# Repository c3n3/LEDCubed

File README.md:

# LEDCubed
LED^3

Hello person who wishes to learn the cube's ways! This will be a BRIEF introduction... Basically the situation is as follows: we have a cube, it is a 12 x 12 x 12 cube of RGB LEDs, we have this newly (but probably old when your reading this) created softare architecture that will hopefully stand the test of time (you decide). The things you want to look into are:
  
  App.h -> this contains the workings for how you make an 'App' for the cube, these can be animations, games, anything...
  The contained class is to be used as an abstract class and not to be used directly.
  
  Basic_Functions.h -> these are the low level functions that allow you to turn LEDs on and change their colors and such

If you fully understand what is in those two files you can start making apps. If you have trouble understanding what is going on just contact me, Caden Churchman, if you can possibly get my information (I'm definitly not writting it here).  

*************************
If you want to bypass the whole structure of the code, feel free to comment out the main loop of arduino and just test stuff there. (Thats probably the best way to learn what the heck is going on)
*************************

TODO:
  - Nest (Wrires)

  - More cool animations

  - 3d tetris

  - 3d minesweeper <----------------------------------- NEXT

  - oscilating 3d graph

  - Glass box

  - Maze/DoomMaze

Done:
  - Add links or files for the KiCad files that made the circuitry

  - Optimize code - Done?

  - Rolling Text Display - Done: TypeEngine

  - Stand - Done
  
  - Power inside stand - Done

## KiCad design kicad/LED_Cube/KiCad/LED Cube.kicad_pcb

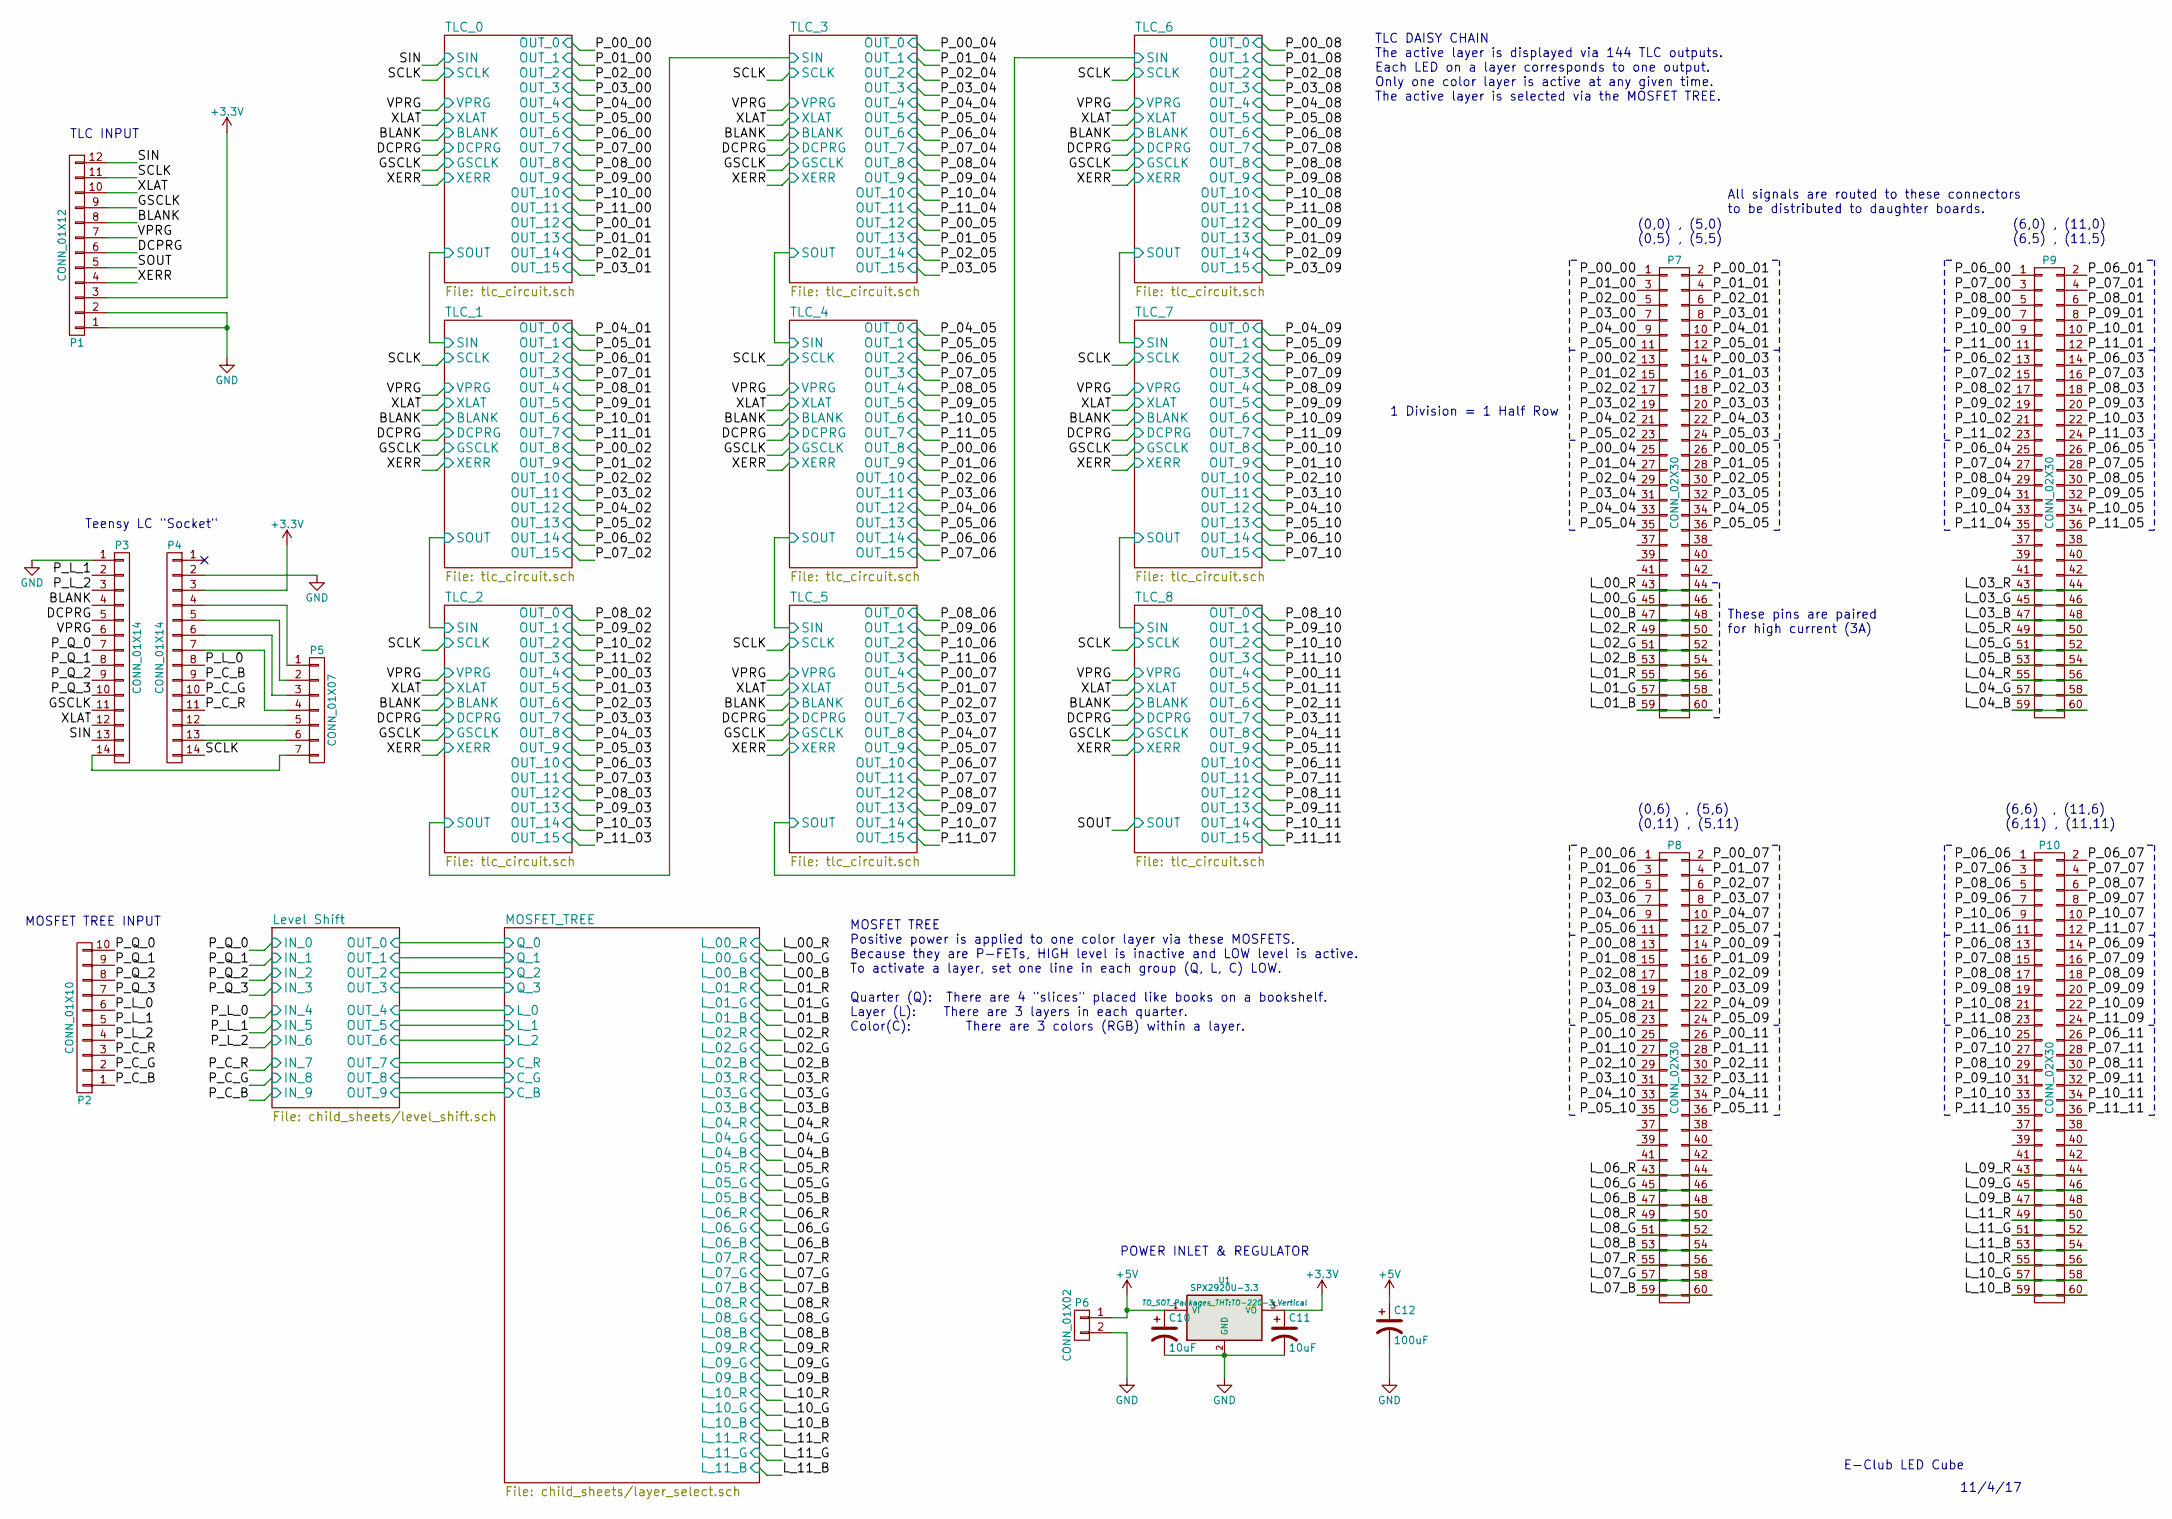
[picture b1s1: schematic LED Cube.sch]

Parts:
C10, C11: 10uF; CP_Radial_D5.0mm_P2.50mm
C12: 100uF; CP_Radial_D8.0mm_P3.50mm
P1: CONN_01X12; Pin_Header_Straight_1x12_Pitch2.54mm
P2: CONN_01X10; Pin_Header_Straight_1x10_Pitch2.54mm
P3, P4: CONN_01X14; Pin_Header_Straight_1x14_Pitch2.54mm
P5: CONN_01X07; Pin_Header_Straight_1x07_Pitch2.54mm
P6: CONN_01X02; TerminalBlock_bornier-2_P5.08mm
P7, P8, P9, P10: CONN_02X30; Pin_Header_Straight_2x30_Pitch2.54mm
U1: SPX2920U-3.3; TO-220-3_Vertical

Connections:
+3V3: C11.1, P1.3, P4.3, U1.3 (VO); also elsewhere on the board
+5V: C10.1, C12.1, P6.1, U1.1 (VI); also elsewhere on the board
/Level Shift/IN_0: P2.10, P3.7; also elsewhere on the board
/Level Shift/IN_1: P2.9, P3.8; also elsewhere on the board
/Level Shift/IN_2: P2.8, P3.9; also elsewhere on the board
/Level Shift/IN_3: P2.7, P3.10; also elsewhere on the board
/Level Shift/IN_4: P2.6, P4.8; also elsewhere on the board
/Level Shift/IN_5: P2.5, P3.2; also elsewhere on the board
/Level Shift/IN_6: P2.4, P3.3; also elsewhere on the board
/Level Shift/IN_7: P2.3, P4.11; also elsewhere on the board
/Level Shift/IN_8: P2.2, P4.10; also elsewhere on the board
/Level Shift/IN_9: P2.1, P4.9; also elsewhere on the board
/MOSFET_TREE/L_00_B: P7.47, P7.48; also elsewhere on the board
/MOSFET_TREE/L_00_G: P7.45, P7.46; also elsewhere on the board
/MOSFET_TREE/L_00_R: P7.43, P7.44; also elsewhere on the board
/MOSFET_TREE/L_01_B: P7.59, P7.60; also elsewhere on the board
/MOSFET_TREE/L_01_G: P7.57, P7.58; also elsewhere on the board
/MOSFET_TREE/L_01_R: P7.55, P7.56; also elsewhere on the board
/MOSFET_TREE/L_02_B: P7.53, P7.54; also elsewhere on the board
/MOSFET_TREE/L_02_G: P7.51, P7.52; also elsewhere on the board
/MOSFET_TREE/L_02_R: P7.49, P7.50; also elsewhere on the board
/MOSFET_TREE/L_03_B: P9.47, P9.48; also elsewhere on the board
/MOSFET_TREE/L_03_G: P9.45, P9.46; also elsewhere on the board
/MOSFET_TREE/L_03_R: P9.43, P9.44; also elsewhere on the board
/MOSFET_TREE/L_04_B: P9.59, P9.60; also elsewhere on the board
/MOSFET_TREE/L_04_G: P9.57, P9.58; also elsewhere on the board
/MOSFET_TREE/L_04_R: P9.55, P9.56; also elsewhere on the board
/MOSFET_TREE/L_05_B: P9.53, P9.54; also elsewhere on the board
/MOSFET_TREE/L_05_G: P9.51, P9.52; also elsewhere on the board
/MOSFET_TREE/L_05_R: P9.49, P9.50; also elsewhere on the board
/MOSFET_TREE/L_06_B: P8.47, P8.48; also elsewhere on the board
/MOSFET_TREE/L_06_G: P8.45, P8.46; also elsewhere on the board
/MOSFET_TREE/L_06_R: P8.43, P8.44; also elsewhere on the board
/MOSFET_TREE/L_07_B: P8.59, P8.60; also elsewhere on the board
/MOSFET_TREE/L_07_G: P8.57, P8.58; also elsewhere on the board
/MOSFET_TREE/L_07_R: P8.55, P8.56; also elsewhere on the board
/MOSFET_TREE/L_08_B: P8.53, P8.54; also elsewhere on the board
/MOSFET_TREE/L_08_G: P8.51, P8.52; also elsewhere on the board
/MOSFET_TREE/L_08_R: P8.49, P8.50; also elsewhere on the board
/MOSFET_TREE/L_09_B: P10.47, P10.48; also elsewhere on the board
/MOSFET_TREE/L_09_G: P10.45, P10.46; also elsewhere on the board
/MOSFET_TREE/L_09_R: P10.43, P10.44; also elsewhere on the board
/MOSFET_TREE/L_10_B: P10.59, P10.60; also elsewhere on the board
/MOSFET_TREE/L_10_G: P10.57, P10.58; also elsewhere on the board
/MOSFET_TREE/L_10_R: P10.55, P10.56; also elsewhere on the board
/MOSFET_TREE/L_11_B: P10.53, P10.54; also elsewhere on the board
/MOSFET_TREE/L_11_G: P10.51, P10.52; also elsewhere on the board
/MOSFET_TREE/L_11_R: P10.49, P10.50; also elsewhere on the board
/TLC_0/BLANK: P1.8, P3.4; also elsewhere on the board
/TLC_0/DCPRG: P1.6, P3.5; also elsewhere on the board
/TLC_0/GSCLK: P1.9, P3.11; also elsewhere on the board
/TLC_0/OUT_0: P7.1; also elsewhere on the board
/TLC_0/OUT_1: P7.3; also elsewhere on the board
/TLC_0/OUT_2: P7.5; also elsewhere on the board
/TLC_0/OUT_3: P7.7; also elsewhere on the board
/TLC_0/OUT_4: P7.9; also elsewhere on the board
/TLC_0/OUT_5: P7.11; also elsewhere on the board
/TLC_0/OUT_6: P9.1; also elsewhere on the board
/TLC_0/OUT_7: P9.3; also elsewhere on the board
/TLC_0/OUT_8: P9.5; also elsewhere on the board
/TLC_0/OUT_9: P9.7; also elsewhere on the board
/TLC_0/OUT_10: P9.9; also elsewhere on the board
/TLC_0/OUT_11: P9.11; also elsewhere on the board
/TLC_0/OUT_12: P7.2; also elsewhere on the board
/TLC_0/OUT_13: P7.4; also elsewhere on the board
/TLC_0/OUT_14: P7.6; also elsewhere on the board
/TLC_0/OUT_15: P7.8; also elsewhere on the board
/TLC_0/SCLK: P1.11, P4.14; also elsewhere on the board
/TLC_0/SIN: P1.12, P3.13; also elsewhere on the board
/TLC_0/VPRG: P1.7, P3.6; also elsewhere on the board
/TLC_0/XERR: P1.4; also elsewhere on the board
/TLC_0/XLAT: P1.10, P3.12; also elsewhere on the board
/TLC_1/OUT_0: P7.10; also elsewhere on the board
/TLC_1/OUT_1: P7.12; also elsewhere on the board
/TLC_1/OUT_2: P9.2; also elsewhere on the board
/TLC_1/OUT_3: P9.4; also elsewhere on the board
/TLC_1/OUT_4: P9.6; also elsewhere on the board
/TLC_1/OUT_5: P9.8; also elsewhere on the board
/TLC_1/OUT_6: P9.10; also elsewhere on the board
/TLC_1/OUT_7: P9.12; also elsewhere on the board
/TLC_1/OUT_8: P7.13; also elsewhere on the board
/TLC_1/OUT_9: P7.15; also elsewhere on the board
/TLC_1/OUT_10: P7.17; also elsewhere on the board
/TLC_1/OUT_11: P7.19; also elsewhere on the board
/TLC_1/OUT_12: P7.21; also elsewhere on the board
/TLC_1/OUT_13: P7.23; also elsewhere on the board
/TLC_1/OUT_14: P9.13; also elsewhere on the board
/TLC_1/OUT_15: P9.15; also elsewhere on the board
/TLC_2/OUT_0: P9.17; also elsewhere on the board
/TLC_2/OUT_1: P9.19; also elsewhere on the board
/TLC_2/OUT_2: P9.21; also elsewhere on the board
/TLC_2/OUT_3: P9.23; also elsewhere on the board
/TLC_2/OUT_4: P7.14; also elsewhere on the board
/TLC_2/OUT_5: P7.16; also elsewhere on the board
/TLC_2/OUT_6: P7.18; also elsewhere on the board
/TLC_2/OUT_7: P7.20; also elsewhere on the board
/TLC_2/OUT_8: P7.22; also elsewhere on the board
/TLC_2/OUT_9: P7.24; also elsewhere on the board
/TLC_2/OUT_10: P9.14; also elsewhere on the board
/TLC_2/OUT_11: P9.16; also elsewhere on the board
/TLC_2/OUT_12: P9.18; also elsewhere on the board
/TLC_2/OUT_13: P9.20; also elsewhere on the board
/TLC_2/OUT_14: P9.22; also elsewhere on the board
/TLC_2/OUT_15: P9.24; also elsewhere on the board
/TLC_3/OUT_0: P7.25; also elsewhere on the board
/TLC_3/OUT_1: P7.27; also elsewhere on the board
/TLC_3/OUT_2: P7.29; also elsewhere on the board
/TLC_3/OUT_3: P7.31; also elsewhere on the board
/TLC_3/OUT_4: P7.33; also elsewhere on the board
/TLC_3/OUT_5: P7.35; also elsewhere on the board
/TLC_3/OUT_6: P9.25; also elsewhere on the board
/TLC_3/OUT_7: P9.27; also elsewhere on the board
/TLC_3/OUT_8: P9.29; also elsewhere on the board
/TLC_3/OUT_9: P9.31; also elsewhere on the board
/TLC_3/OUT_10: P9.33; also elsewhere on the board
/TLC_3/OUT_11: P9.35; also elsewhere on the board
/TLC_3/OUT_12: P7.26; also elsewhere on the board
/TLC_3/OUT_13: P7.28; also elsewhere on the board
/TLC_3/OUT_14: P7.30; also elsewhere on the board
/TLC_3/OUT_15: P7.32; also elsewhere on the board
/TLC_4/OUT_0: P7.34; also elsewhere on the board
/TLC_4/OUT_1: P7.36; also elsewhere on the board
/TLC_4/OUT_2: P9.26; also elsewhere on the board
/TLC_4/OUT_3: P9.28; also elsewhere on the board
/TLC_4/OUT_4: P9.30; also elsewhere on the board
/TLC_4/OUT_5: P9.32; also elsewhere on the board
/TLC_4/OUT_6: P9.34; also elsewhere on the board
/TLC_4/OUT_7: P9.36; also elsewhere on the board
/TLC_4/OUT_8: P8.1; also elsewhere on the board
/TLC_4/OUT_9: P8.3; also elsewhere on the board
/TLC_4/OUT_10: P8.5; also elsewhere on the board
/TLC_4/OUT_11: P8.7; also elsewhere on the board
/TLC_4/OUT_12: P8.9; also elsewhere on the board
/TLC_4/OUT_13: P8.11; also elsewhere on the board
/TLC_4/OUT_14: P10.1; also elsewhere on the board
/TLC_4/OUT_15: P10.3; also elsewhere on the board
/TLC_5/OUT_0: P10.5; also elsewhere on the board
/TLC_5/OUT_1: P10.7; also elsewhere on the board
/TLC_5/OUT_2: P10.9; also elsewhere on the board
/TLC_5/OUT_3: P10.11; also elsewhere on the board
/TLC_5/OUT_4: P8.2; also elsewhere on the board
/TLC_5/OUT_5: P8.4; also elsewhere on the board
/TLC_5/OUT_6: P8.6; also elsewhere on the board
/TLC_5/OUT_7: P8.8; also elsewhere on the board
/TLC_5/OUT_8: P8.10; also elsewhere on the board
/TLC_5/OUT_9: P8.12; also elsewhere on the board
/TLC_5/OUT_10: P10.2; also elsewhere on the board
/TLC_5/OUT_11: P10.4; also elsewhere on the board
/TLC_5/OUT_12: P10.6; also elsewhere on the board
/TLC_5/OUT_13: P10.8; also elsewhere on the board
/TLC_5/OUT_14: P10.10; also elsewhere on the board
/TLC_5/OUT_15: P10.12; also elsewhere on the board
/TLC_6/OUT_0: P8.13; also elsewhere on the board
/TLC_6/OUT_1: P8.15; also elsewhere on the board
/TLC_6/OUT_2: P8.17; also elsewhere on the board
/TLC_6/OUT_3: P8.19; also elsewhere on the board
/TLC_6/OUT_4: P8.21; also elsewhere on the board
/TLC_6/OUT_5: P8.23; also elsewhere on the board
/TLC_6/OUT_6: P10.13; also elsewhere on the board
/TLC_6/OUT_7: P10.15; also elsewhere on the board
/TLC_6/OUT_8: P10.17; also elsewhere on the board
/TLC_6/OUT_9: P10.19; also elsewhere on the board
/TLC_6/OUT_10: P10.21; also elsewhere on the board
/TLC_6/OUT_11: P10.23; also elsewhere on the board
/TLC_6/OUT_12: P8.14; also elsewhere on the board
/TLC_6/OUT_13: P8.16; also elsewhere on the board
/TLC_6/OUT_14: P8.18; also elsewhere on the board
/TLC_6/OUT_15: P8.20; also elsewhere on the board
/TLC_7/OUT_0: P8.22; also elsewhere on the board
/TLC_7/OUT_1: P8.24; also elsewhere on the board
/TLC_7/OUT_2: P10.14; also elsewhere on the board
/TLC_7/OUT_3: P10.16; also elsewhere on the board
/TLC_7/OUT_4: P10.18; also elsewhere on the board
/TLC_7/OUT_5: P10.20; also elsewhere on the board
/TLC_7/OUT_6: P10.22; also elsewhere on the board
/TLC_7/OUT_7: P10.24; also elsewhere on the board
/TLC_7/OUT_8: P8.25; also elsewhere on the board
/TLC_7/OUT_9: P8.27; also elsewhere on the board
/TLC_7/OUT_10: P8.29; also elsewhere on the board
/TLC_7/OUT_11: P8.31; also elsewhere on the board
/TLC_7/OUT_12: P8.33; also elsewhere on the board
/TLC_7/OUT_13: P8.35; also elsewhere on the board
/TLC_7/OUT_14: P10.25; also elsewhere on the board
/TLC_7/OUT_15: P10.27; also elsewhere on the board
/TLC_8/OUT_0: P10.29; also elsewhere on the board
/TLC_8/OUT_1: P10.31; also elsewhere on the board
/TLC_8/OUT_2: P10.33; also elsewhere on the board
/TLC_8/OUT_3: P10.35; also elsewhere on the board
/TLC_8/OUT_4: P8.26; also elsewhere on the board
/TLC_8/OUT_5: P8.28; also elsewhere on the board
/TLC_8/OUT_6: P8.30; also elsewhere on the board
/TLC_8/OUT_7: P8.32; also elsewhere on the board
/TLC_8/OUT_8: P8.34; also elsewhere on the board
/TLC_8/OUT_9: P8.36; also elsewhere on the board
/TLC_8/OUT_10: P10.26; also elsewhere on the board
/TLC_8/OUT_11: P10.28; also elsewhere on the board
/TLC_8/OUT_12: P10.30; also elsewhere on the board
/TLC_8/OUT_13: P10.32; also elsewhere on the board
/TLC_8/OUT_14: P10.34; also elsewhere on the board
/TLC_8/OUT_15: P10.36; also elsewhere on the board
/TLC_8/SOUT: P1.5; also elsewhere on the board
GND: C10.2, C11.2, C12.2, P1.1, P1.2, P3.1, P4.2, P6.2, U1.2 (GND); also elsewhere on the board
unnamed: P3.14, P5.7
unnamed: P4.4, P5.1
unnamed: P4.5, P5.2
unnamed: P4.6, P5.3
unnamed: P4.7, P5.4
unnamed: P4.12, P5.5
unnamed: P4.13, P5.6

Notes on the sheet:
E-Club LED Cube
11/4/17
(0,0) , (5,0) (0,5) , (5,5)
(6,0) , (11,0) (6,5) , (11,5)
(0,6) , (5,6) (0,11) , (5,11)
(6,6) , (11,6) (6,11) , (11,11)
MOSFET TREE Positive power is applied to one color layer via these MOSFETS. Because they are P-FETs, HIGH level is inactive and LOW level is active. To activate a layer, set one line in each group (Q, L, C) LOW. Quarter (Q): There are 4 "slices" placed like books on a bookshelf. Layer (L): There ar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
TLC DAISY CHAIN The active layer is displayed via 144 TLC outputs. Each LED on a layer corresponds to one output. Only one color layer is active at any given time. The active layer is selected via the MOSFET TREE.
All signals are routed to these connectors to be distributed to daughter boards.
POWER INLET & REGULATOR
TLC INPUT
MOSFET TREE INPUT
1 Division = 1 Half Row
Teensy LC "Socket"
These pins are paired for high current (3A)

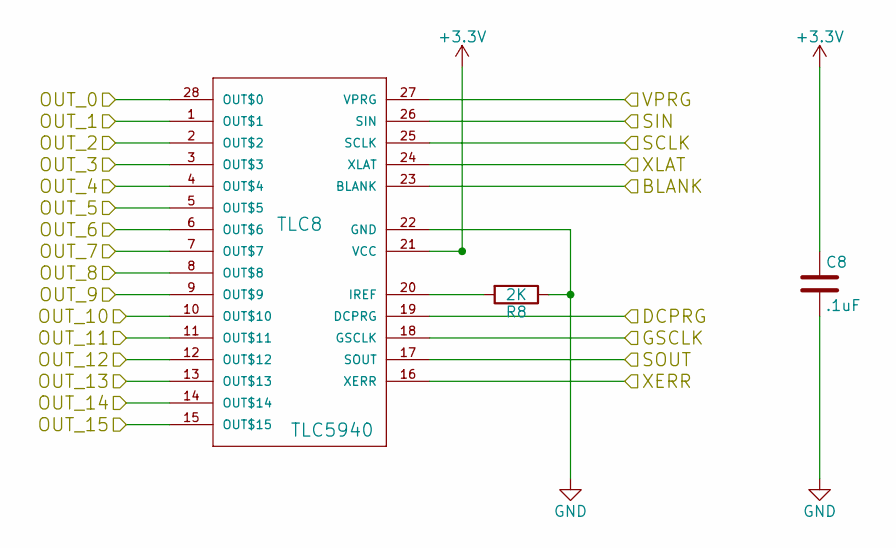
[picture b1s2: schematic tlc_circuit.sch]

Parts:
C1: .1uF; R_0805_HandSoldering
R1: 2K; R_0805_HandSoldering
TLC4: TLC5940; DIP-28_W7.62mm_Socket

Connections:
+3V3: C1.1, TLC4.21 (VCC); also elsewhere on the board
/TLC_0/BLANK: TLC4.23 (BLANK); also elsewhere on the board
/TLC_0/DCPRG: TLC4.19 (DCPRG); also elsewhere on the board
/TLC_0/GSCLK: TLC4.18 (GSCLK); also elsewhere on the board
/TLC_0/SCLK: TLC4.25 (SCLK); also elsewhere on the board
/TLC_0/VPRG: TLC4.27 (VPRG); also elsewhere on the board
/TLC_0/XERR: TLC4.16 (XERR); also elsewhere on the board
/TLC_0/XLAT: TLC4.24 (XLAT); also elsewhere on the board
/TLC_3/OUT_0: TLC4.28 (OUT$0); also elsewhere on the board
/TLC_3/OUT_1: TLC4.1 (OUT$1); also elsewhere on the board
/TLC_3/OUT_2: TLC4.2 (OUT$2); also elsewhere on the board
/TLC_3/OUT_3: TLC4.3 (OUT$3); also elsewhere on the board
/TLC_3/OUT_4: TLC4.4 (OUT$4); also elsewhere on the board
/TLC_3/OUT_5: TLC4.5 (OUT$5); also elsewhere on the board
/TLC_3/OUT_6: TLC4.6 (OUT$6); also elsewhere on the board
/TLC_3/OUT_7: TLC4.7 (OUT$7); also elsewhere on the board
/TLC_3/OUT_8: TLC4.8 (OUT$8); also elsewhere on the board
/TLC_3/OUT_9: TLC4.9 (OUT$9); also elsewhere on the board
/TLC_3/OUT_10: TLC4.10 (OUT$10); also elsewhere on the board
/TLC_3/OUT_11: TLC4.11 (OUT$11); also elsewhere on the board
/TLC_3/OUT_12: TLC4.12 (OUT$12); also elsewhere on the board
/TLC_3/OUT_13: TLC4.13 (OUT$13); also elsewhere on the board
/TLC_3/OUT_14: TLC4.14 (OUT$14); also elsewhere on the board
/TLC_3/OUT_15: TLC4.15 (OUT$15); also elsewhere on the board
/TLC_3/SIN: TLC4.26 (SIN); also elsewhere on the board
/TLC_4/SIN: TLC4.17 (SOUT); also elsewhere on the board
GND: C1.2, R1.1, TLC4.22 (GND); also elsewhere on the board

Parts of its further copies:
C2, C3, C4, C5, C6, C7, C8, C9: .1uF; R_0805_HandSoldering
R2, R3, R4, R5, R6, R7, R8, R9: 2K; R_0805_HandSoldering
TLC1, TLC2, TLC3, TLC5, TLC6, TLC7, TLC8, TLC9: TLC5940; DIP-28_W7.62mm_Socket

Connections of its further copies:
+3V3: C2.1, C3.1, C4.1, C5.1, C6.1, C7.1, C8.1, C9.1, TLC1.21 (VCC), TLC2.21 (VCC), TLC3.21 (VCC), TLC5.21 (VCC), TLC6.21 (VCC), TLC7.21 (VCC), TLC8.21 (VCC), TLC9.21 (VCC); also elsewhere on the board
/TLC_0/BLANK: TLC1.23 (BLANK), TLC2.23 (BLANK), TLC3.23 (BLANK), TLC5.23 (BLANK), TLC6.23 (BLANK), TLC7.23 (BLANK), TLC8.23 (BLANK), TLC9.23 (BLANK); also elsewhere on the board
/TLC_0/DCPRG: TLC1.19 (DCPRG), TLC2.19 (DCPRG), TLC3.19 (DCPRG), TLC5.19 (DCPRG), TLC6.19 (DCPRG), TLC7.19 (DCPRG), TLC8.19 (DCPRG), TLC9.19 (DCPRG); also elsewhere on the board
/TLC_0/GSCLK: TLC1.18 (GSCLK), TLC2.18 (GSCLK), TLC3.18 (GSCLK), TLC5.18 (GSCLK), TLC6.18 (GSCLK), TLC7.18 (GSCLK), TLC8.18 (GSCLK), TLC9.18 (GSCLK); also elsewhere on the board
/TLC_0/OUT_0: TLC1.28 (OUT$0); also elsewhere on the board
/TLC_0/OUT_1: TLC1.1 (OUT$1); also elsewhere on the board
/TLC_0/OUT_2: TLC1.2 (OUT$2); also elsewhere on the board
/TLC_0/OUT_3: TLC1.3 (OUT$3); also elsewhere on the board
/TLC_0/OUT_4: TLC1.4 (OUT$4); also elsewhere on the board
/TLC_0/OUT_5: TLC1.5 (OUT$5); also elsewhere on the board
/TLC_0/OUT_6: TLC1.6 (OUT$6); also elsewhere on the board
/TLC_0/OUT_7: TLC1.7 (OUT$7); also elsewhere on the board
/TLC_0/OUT_8: TLC1.8 (OUT$8); also elsewhere on the board
/TLC_0/OUT_9: TLC1.9 (OUT$9); also elsewhere on the board
/TLC_0/OUT_10: TLC1.10 (OUT$10); also elsewhere on the board
/TLC_0/OUT_11: TLC1.11 (OUT$11); also elsewhere on the board
/TLC_0/OUT_12: TLC1.12 (OUT$12); also elsewhere on the board
/TLC_0/OUT_13: TLC1.13 (OUT$13); also elsewhere on the board
/TLC_0/OUT_14: TLC1.14 (OUT$14); also elsewhere on the board
/TLC_0/OUT_15: TLC1.15 (OUT$15); also elsewhere on the board
/TLC_0/SCLK: TLC1.25 (SCLK), TLC2.25 (SCLK), TLC3.25 (SCLK), TLC5.25 (SCLK), TLC6.25 (SCLK), TLC7.25 (SCLK), TLC8.25 (SCLK), TLC9.25 (SCLK); also elsewhere on the board
/TLC_0/SIN: TLC1.26 (SIN); also elsewhere on the board
/TLC_0/VPRG: TLC1.27 (VPRG), TLC2.27 (VPRG), TLC3.27 (VPRG), TLC5.27 (VPRG), TLC6.27 (VPRG), TLC7.27 (VPRG), TLC8.27 (VPRG), TLC9.27 (VPRG); also elsewhere on the board
/TLC_0/XERR: TLC1.16 (XERR), TLC2.16 (XERR), TLC3.16 (XERR), TLC5.16 (XERR), TLC6.16 (XERR), TLC7.16 (XERR), TLC8.16 (XERR), TLC9.16 (XERR); also elsewhere on the board
/TLC_0/XLAT: TLC1.24 (XLAT), TLC2.24 (XLAT), TLC3.24 (XLAT), TLC5.24 (XLAT), TLC6.24 (XLAT), TLC7.24 (XLAT), TLC8.24 (XLAT), TLC9.24 (XLAT); also elsewhere on the board
/TLC_1/OUT_0: TLC2.28 (OUT$0); also elsewhere on the board
/TLC_1/OUT_1: TLC2.1 (OUT$1); also elsewhere on the board
/TLC_1/OUT_2: TLC2.2 (OUT$2); also elsewhere on the board
/TLC_1/OUT_3: TLC2.3 (OUT$3); also elsewhere on the board
/TLC_1/OUT_4: TLC2.4 (OUT$4); also elsewhere on the board
/TLC_1/OUT_5: TLC2.5 (OUT$5); also elsewhere on the board
/TLC_1/OUT_6: TLC2.6 (OUT$6); also elsewhere on the board
/TLC_1/OUT_7: TLC2.7 (OUT$7); also elsewhere on the board
/TLC_1/OUT_8: TLC2.8 (OUT$8); also elsewhere on the board
/TLC_1/OUT_9: TLC2.9 (OUT$9); also elsewhere on the board
/TLC_1/OUT_10: TLC2.10 (OUT$10); also elsewhere on the board
/TLC_1/OUT_11: TLC2.11 (OUT$11); also elsewhere on the board
/TLC_1/OUT_12: TLC2.12 (OUT$12); also elsewhere on the board
/TLC_1/OUT_13: TLC2.13 (OUT$13); also elsewhere on the board
/TLC_1/OUT_14: TLC2.14 (OUT$14); also elsewhere on the board
/TLC_1/OUT_15: TLC2.15 (OUT$15); also elsewhere on the board
/TLC_1/SIN: TLC1.17 (SOUT), TLC2.26 (SIN)
/TLC_2/OUT_0: TLC3.28 (OUT$0); also elsewhere on the board
/TLC_2/OUT_1: TLC3.1 (OUT$1); also elsewhere on the board
/TLC_2/OUT_2: TLC3.2 (OUT$2); also elsewhere on the board
/TLC_2/OUT_3: TLC3.3 (OUT$3); also elsewhere on the board
/TLC_2/OUT_4: TLC3.4 (OUT$4); also elsewhere on the board
/TLC_2/OUT_5: TLC3.5 (OUT$5); also elsewhere on the board
/TLC_2/OUT_6: TLC3.6 (OUT$6); also elsewhere on the board
/TLC_2/OUT_7: TLC3.7 (OUT$7); also elsewhere on the board
/TLC_2/OUT_8: TLC3.8 (OUT$8); also elsewhere on the board
/TLC_2/OUT_9: TLC3.9 (OUT$9); also elsewhere on the board
/TLC_2/OUT_10: TLC3.10 (OUT$10); also elsewhere on the board
/TLC_2/OUT_11: TLC3.11 (OUT$11); also elsewhere on the board
/TLC_2/OUT_12: TLC3.12 (OUT$12); also elsewhere on the board
/TLC_2/OUT_13: TLC3.13 (OUT$13); also elsewhere on the board
/TLC_2/OUT_14: TLC3.14 (OUT$14); also elsewhere on the board
/TLC_2/OUT_15: TLC3.15 (OUT$15); also elsewhere on the board
/TLC_2/SIN: TLC2.17 (SOUT), TLC3.26 (SIN)
/TLC_3/SIN: TLC3.17 (SOUT); also elsewhere on the board
/TLC_4/OUT_0: TLC5.28 (OUT$0); also elsewhere on the board
/TLC_4/OUT_1: TLC5.1 (OUT$1); also elsewhere on the board
/TLC_4/OUT_2: TLC5.2 (OUT$2); also elsewhere on the board
/TLC_4/OUT_3: TLC5.3 (OUT$3); also elsewhere on the board
/TLC_4/OUT_4: TLC5.4 (OUT$4); also elsewhere on the board
/TLC_4/OUT_5: TLC5.5 (OUT$5); also elsewhere on the board
/TLC_4/OUT_6: TLC5.6 (OUT$6); also elsewhere on the board
/TLC_4/OUT_7: TLC5.7 (OUT$7); also elsewhere on the board
/TLC_4/OUT_8: TLC5.8 (OUT$8); also elsewhere on the board
/TLC_4/OUT_9: TLC5.9 (OUT$9); also elsewhere on the board
/TLC_4/OUT_10: TLC5.10 (OUT$10); also elsewhere on the board
/TLC_4/OUT_11: TLC5.11 (OUT$11); also elsewhere on the board
/TLC_4/OUT_12: TLC5.12 (OUT$12); also elsewhere on the board
/TLC_4/OUT_13: TLC5.13 (OUT$13); also elsewhere on the board
/TLC_4/OUT_14: TLC5.14 (OUT$14); also elsewhere on the board
/TLC_4/OUT_15: TLC5.15 (OUT$15); also elsewhere on the board
/TLC_4/SIN: TLC5.26 (SIN); also elsewhere on the board
/TLC_5/OUT_0: TLC6.28 (OUT$0); also elsewhere on the board
/TLC_5/OUT_1: TLC6.1 (OUT$1); also elsewhere on the board
/TLC_5/OUT_2: TLC6.2 (OUT$2); also elsewhere on the board
/TLC_5/OUT_3: TLC6.3 (OUT$3); also elsewhere on the board
/TLC_5/OUT_4: TLC6.4 (OUT$4); also elsewhere on the board
/TLC_5/OUT_5: TLC6.5 (OUT$5); also elsewhere on the board
/TLC_5/OUT_6: TLC6.6 (OUT$6); also elsewhere on the board
/TLC_5/OUT_7: TLC6.7 (OUT$7); also elsewhere on the board
/TLC_5/OUT_8: TLC6.8 (OUT$8); also elsewhere on the board
/TLC_5/OUT_9: TLC6.9 (OUT$9); also elsewhere on the board
/TLC_5/OUT_10: TLC6.10 (OUT$10); also elsewhere on the board
/TLC_5/OUT_11: TLC6.11 (OUT$11); also elsewhere on the board
/TLC_5/OUT_12: TLC6.12 (OUT$12); also elsewhere on the board
/TLC_5/OUT_13: TLC6.13 (OUT$13); also elsewhere on the board
/TLC_5/OUT_14: TLC6.14 (OUT$14); also elsewhere on the board
/TLC_5/OUT_15: TLC6.15 (OUT$15); also elsewhere on the board
/TLC_5/SIN: TLC5.17 (SOUT), TLC6.26 (SIN)
/TLC_6/OUT_0: TLC7.28 (OUT$0); also elsewhere on the board
/TLC_6/OUT_1: TLC7.1 (OUT$1); also elsewhere on the board
/TLC_6/OUT_2: TLC7.2 (OUT$2); also elsewhere on the board
/TLC_6/OUT_3: TLC7.3 (OUT$3); also elsewhere on the board
/TLC_6/OUT_4: TLC7.4 (OUT$4); also elsewhere on the board
/TLC_6/OUT_5: TLC7.5 (OUT$5); also elsewhere on the board
/TLC_6/OUT_6: TLC7.6 (OUT$6); also elsewhere on the board
/TLC_6/OUT_7: TLC7.7 (OUT$7); also elsewhere on the board
/TLC_6/OUT_8: TLC7.8 (OUT$8); also elsewhere on the board
/TLC_6/OUT_9: TLC7.9 (OUT$9); also elsewhere on the board
/TLC_6/OUT_10: TLC7.10 (OUT$10); also elsewhere on the board
/TLC_6/OUT_11: TLC7.11 (OUT$11); also elsewhere on the board
/TLC_6/OUT_12: TLC7.12 (OUT$12); also elsewhere on the board
/TLC_6/OUT_13: TLC7.13 (OUT$13); also elsewhere on the board
/TLC_6/OUT_14: TLC7.14 (OUT$14); also elsewhere on the board
/TLC_6/OUT_15: TLC7.15 (OUT$15); also elsewhere on the board
/TLC_6/SIN: TLC6.17 (SOUT), TLC7.26 (SIN)
/TLC_7/OUT_0: TLC8.28 (OUT$0); also elsewhere on the board
/TLC_7/OUT_1: TLC8.1 (OUT$1); also elsewhere on the board
/TLC_7/OUT_2: TLC8.2 (OUT$2); also elsewhere on the board
/TLC_7/OUT_3: TLC8.3 (OUT$3); also elsewhere on the board
/TLC_7/OUT_4: TLC8.4 (OUT$4); also elsewhere on the board
/TLC_7/OUT_5: TLC8.5 (OUT$5); also elsewhere on the board
/TLC_7/OUT_6: TLC8.6 (OUT$6); also elsewhere on the board
/TLC_7/OUT_7: TLC8.7 (OUT$7); also elsewhere on the board
/TLC_7/OUT_8: TLC8.8 (OUT$8); also elsewhere on the board
/TLC_7/OUT_9: TLC8.9 (OUT$9); also elsewhere on the board
/TLC_7/OUT_10: TLC8.10 (OUT$10); also elsewhere on the board
/TLC_7/OUT_11: TLC8.11 (OUT$11); also elsewhere on the board
/TLC_7/OUT_12: TLC8.12 (OUT$12); also elsewhere on the board
/TLC_7/OUT_13: TLC8.13 (OUT$13); also elsewhere on the board
/TLC_7/OUT_14: TLC8.14 (OUT$14); also elsewhere on the board
/TLC_7/OUT_15: TLC8.15 (OUT$15); also elsewhere on the board
/TLC_7/SIN: TLC7.17 (SOUT), TLC8.26 (SIN)
/TLC_8/OUT_0: TLC9.28 (OUT$0); also elsewhere on the board
/TLC_8/OUT_1: TLC9.1 (OUT$1); also elsewhere on the board
/TLC_8/OUT_2: TLC9.2 (OUT$2); also elsewhere on the board
/TLC_8/OUT_3: TLC9.3 (OUT$3); also elsewhere on the board
/TLC_8/OUT_4: TLC9.4 (OUT$4); also elsewhere on the board
/TLC_8/OUT_5: TLC9.5 (OUT$5); also elsewhere on the board
/TLC_8/OUT_6: TLC9.6 (OUT$6); also elsewhere on the board
/TLC_8/OUT_7: TLC9.7 (OUT$7); also elsewhere on the board
/TLC_8/OUT_8: TLC9.8 (OUT$8); also elsewhere on the board
/TLC_8/OUT_9: TLC9.9 (OUT$9); also elsewhere on the board
/TLC_8/OUT_10: TLC9.10 (OUT$10); also elsewhere on the board
/TLC_8/OUT_11: TLC9.11 (OUT$11); also elsewhere on the board
/TLC_8/OUT_12: TLC9.12 (OUT$12); also elsewhere on the board
/TLC_8/OUT_13: TLC9.13 (OUT$13); also elsewhere on the board
/TLC_8/OUT_14: TLC9.14 (OUT$14); also elsewhere on the board
/TLC_8/OUT_15: TLC9.15 (OUT$15); also elsewhere on the board
/TLC_8/SIN: TLC8.17 (SOUT), TLC9.26 (SIN)
/TLC_8/SOUT: TLC9.17 (SOUT); also elsewhere on the board
GND: C2.2, C3.2, C4.2, C5.2, C6.2, C7.2, C8.2, C9.2, R2.1, R3.1, R4.1, R5.1, R6.1, R7.1, R8.1, R9.1, TLC1.22 (GND), TLC2.22 (GND), TLC3.22 (GND), TLC5.22 (GND), TLC6.22 (GND), TLC7.22 (GND), TLC8.22 (GND), TLC9.22 (GND); also elsewhere on the board
unnamed: R2.2, TLC2.20 (IREF)
unnamed: R3.2, TLC3.20 (IREF)
unnamed: R5.2, TLC5.20 (IREF)
unnamed: R6.2, TLC6.20 (IREF)
unnamed: R7.2, TLC7.20 (IREF)
unnamed: R8.2, TLC8.20 (IREF)
unnamed: R9.2, TLC9.20 (IREF)

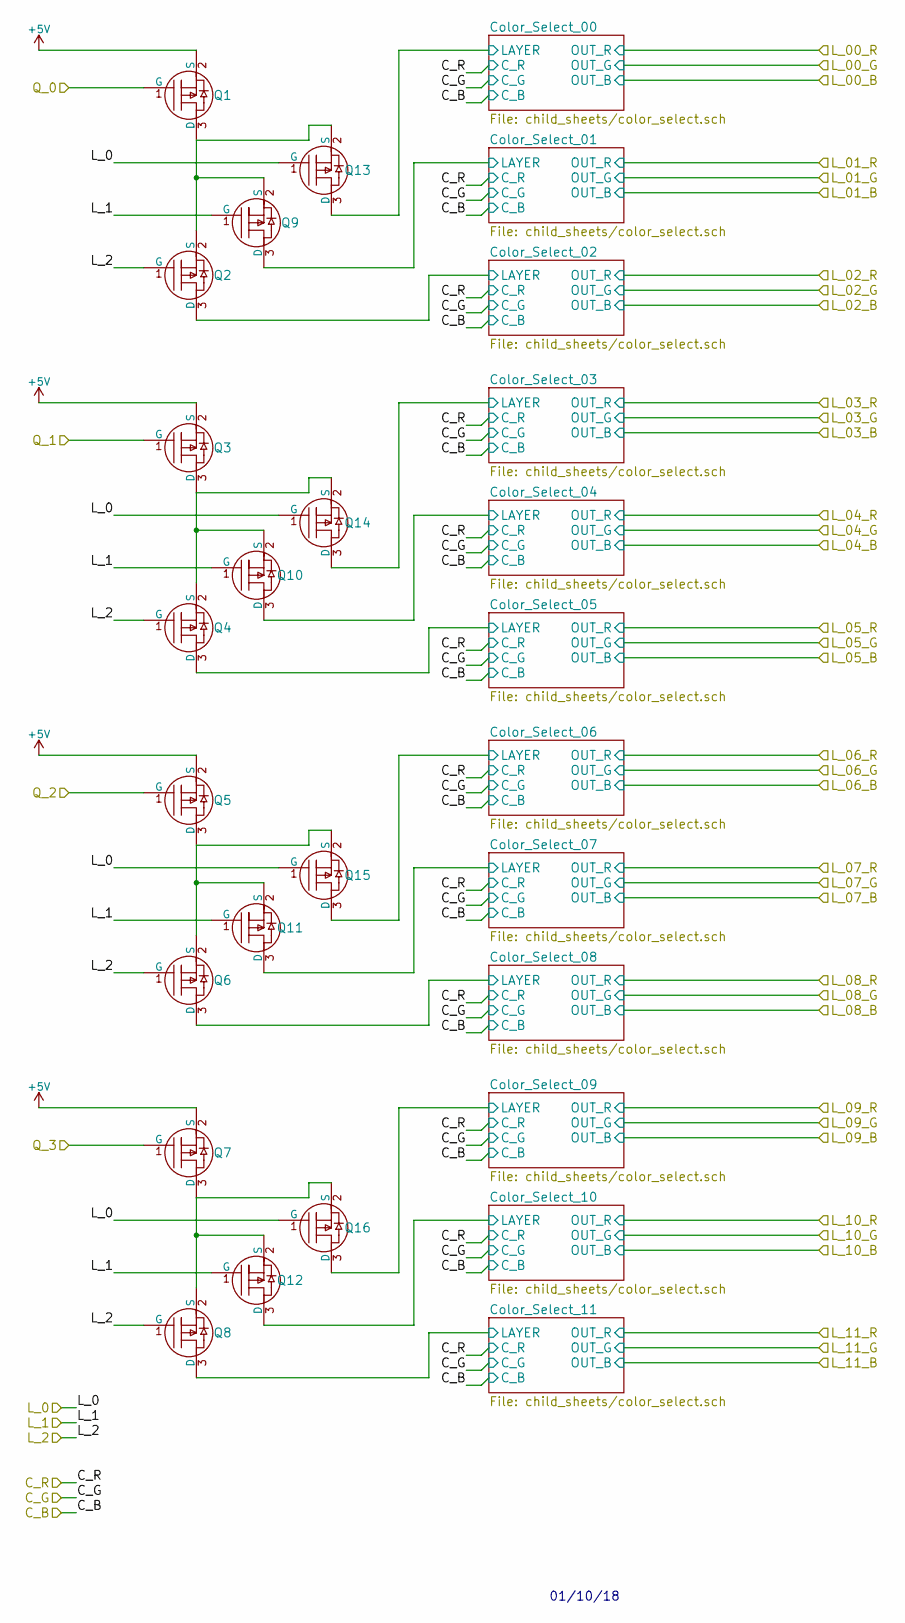
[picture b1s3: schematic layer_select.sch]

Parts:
Q1, Q2, Q3, Q4, Q5, Q6, Q7, Q8, Q9, Q10, Q11, Q12, Q13, Q14, Q15, Q16: P-Channel_MOSFET; SOT-23

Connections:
+5V: Q1.2 (S), Q3.2 (S), Q5.2 (S), Q7.2 (S); also elsewhere on the board
/Level Shift/OUT_0: Q1.1 (G); also elsewhere on the board
/Level Shift/OUT_1: Q3.1 (G); also elsewhere on the board
/Level Shift/OUT_2: Q5.1 (G); also elsewhere on the board
/Level Shift/OUT_3: Q7.1 (G); also elsewhere on the board
/MOSFET_TREE/Color_Select_00/LAYER: Q13.3 (D); also elsewhere on the board
/MOSFET_TREE/Color_Select_01/LAYER: Q9.3 (D); also elsewhere on the board
/MOSFET_TREE/Color_Select_02/LAYER: Q2.3 (D); also elsewhere on the board
/MOSFET_TREE/Color_Select_03/LAYER: Q14.3 (D); also elsewhere on the board
/MOSFET_TREE/Color_Select_04/LAYER: Q10.3 (D); also elsewhere on the board
/MOSFET_TREE/Color_Select_05/LAYER: Q4.3 (D); also elsewhere on the board
/MOSFET_TREE/Color_Select_06/LAYER: Q15.3 (D); also elsewhere on the board
/MOSFET_TREE/Color_Select_07/LAYER: Q11.3 (D); also elsewhere on the board
/MOSFET_TREE/Color_Select_08/LAYER: Q6.3 (D); also elsewhere on the board
/MOSFET_TREE/Color_Select_09/LAYER: Q16.3 (D); also elsewhere on the board
/MOSFET_TREE/Color_Select_10/LAYER: Q12.3 (D); also elsewhere on the board
/MOSFET_TREE/Color_Select_11/LAYER: Q8.3 (D); also elsewhere on the board
/MOSFET_TREE/L_0: Q13.1 (G), Q14.1 (G), Q15.1 (G), Q16.1 (G); also elsewhere on the board
/MOSFET_TREE/L_1: Q9.1 (G), Q10.1 (G), Q11.1 (G), Q12.1 (G); also elsewhere on the board
/MOSFET_TREE/L_2: Q2.1 (G), Q4.1 (G), Q6.1 (G), Q8.1 (G); also elsewhere on the board
unnamed: Q1.3 (D), Q2.2 (S), Q9.2 (S), Q13.2 (S)
unnamed: Q3.3 (D), Q4.2 (S), Q10.2 (S), Q14.2 (S)
unnamed: Q5.3 (D), Q6.2 (S), Q11.2 (S), Q15.2 (S)
unnamed: Q7.3 (D), Q8.2 (S), Q12.2 (S), Q16.2 (S)

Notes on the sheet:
01/10/18
